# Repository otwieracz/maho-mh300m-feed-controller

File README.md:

# MAHO MH300M Feedrate Controller

## 1. Introduction

### 1.1 Purpose

The MH300M Feedrate Controller is designed to precisely align the panel readings for feed control on the MAHO MH300M milling machine with the voltage output for the tachogenerator. This ensures that the machine operates with accurate and reliable feed rates after the original BBbC LE 10 b-E driver was replaced with a Parker 512C driver.

### 1.2 Overview

This device is retrofitted into the control box of the MAHO MH300M, requiring no changes to the existing wiring. It connects to the Parker 512C driver, the machine's potentiometer, and the control panel's RAPID and CREEP (1/100) buttons. The device converts arbitrary potentiometer values into a calibrated voltage output, ensuring that the machine's feed rates are consistent and accurate.

### 1.3 MAHO MH300M Control Panel

10. Creep feed rate switch (1/1 - 1/100). *Note: MAHO MH300M Feedrate Controller reduces the feed rate by a factor of 10 instead of 100 when in Creep Mode.*
11. Rapid feed rate switch.
12. Feedrate potentiometer.

## 2. Device Components and Connections

### 2.1 Connectors

The device has the following connectors:

- **512C Connector**: 
  - +10V Reference (maximum 5mA)
  - Analog Setpoint (output from the device)
  - Ground (GND)
- **Potentiometer Connector**: Connects to the machine's potentiometer.
- **RAPID and CREEP Button Connectors**: Connects to the control panel's RAPID and CREEP (1/100) buttons.
- **Clear EEPROM Button**: Used to reset the device's configuration stored in EEPROM.

### 2.2 LED Indicator

The device includes an LED indicator used to convey various status messages during setup and operation. The LED blinks in specific patterns to communicate different messages.

## 3. Configuration and Calibration

### 3.1 Initial Setup

Upon installation, the device requires calibration to match the feed rates of the milling machine with the appropriate voltage output. This calibration process is stored in the device's EEPROM, ensuring that the settings persist even after power cycles.

### 3.2 Clearing EEPROM

If you need to reset the device to its default configuration, press and hold the **Clear EEPROM** button while powering on the device. This will erase all stored settings and reset the device to its factory state.

**Note:** Clearing the EEPROM will require recalibration.

### 3.3 Calibration Procedures

Calibration is done in two main steps: configuring the digital potentiometer and setting the ADC steps.

#### 3.3.1 Digital Potentiometer Calibration

1. **Minimum Feed Rate Calibration**: 
   - The **Minimum Feed Rate** is the lowest feed rate at which the milling machine can operate stably. This feed rate is crucial as it ensures that the machine can perform slow movements without stalling, particularly under heavy loads.
   - To accurately determine the minimum feed rate, it's recommended to run all axes simultaneously, especially the Z-axis moving upward, as this simulates the heaviest load.
   - The device will enter the calibration mode for the minimum feed rate (in mm/min).
   - The LED will blink a long-short pattern (`-.`).
   - The device reads the analog input for 30 seconds to determine the minimum digital potentiometer value necessary to maintain stable operation.

2. **500 mm/min Feed Rate Calibration**:
   - The 500 mm/min feed rate serves as a key reference point. This feed rate corresponds to a voltage output of **4.16V** at the terminals of the Parker 512C.
   - The LED will blink a short-long pattern (`.-`).
   - To accurately measure this, connect a voltmeter to the 512C terminals to account for any voltage drop between the control box and the driver.
   - The device adjusts the potentiometer until the voltmeter reads exactly 4.16V, ensuring that the machine's feed rate is precisely 500 mm/min.

#### 3.3.2 ADC Steps Calibration

The device divides the feed rate range into 16 steps, each representing a specific feed rate.

1. **Step Calibration**:
   - For each step, the device reads the analog input for 5.5 seconds.
   - The LED will blink a long-long pattern (`--`) during each step.
   - For each step, set the potentiometer `10` on control panel to the corresponding feed rate (0, 12.5, 20, 31, 40, 50, 63, 80, 100, 125, 160, 200, 250, 315, 400, 500 mm/min).
   - The device will automatically store the ADC value corresponding to each feed rate in the EEPROM.

#### 3.3.3 EEPROM Storage

Once calibration is complete, the device will store the configuration in EEPROM, indicated by two short blinks (`..`). The device will then use this configuration to convert potentiometer values into the appropriate voltage output.

### 3.4 Manual Calibration and Monitoring via UART

#### 3.4.1 Overview

The UART interface is the primary method for monitoring and configuring the MH300M Feedrate Controller. This interface allows you to observe real-time status messages during the calibration process and verify the configuration settings. You can use any UART-capable device, such as a USB-to-UART adapter or a device like the Flipper Zero, to connect to the controller and monitor the serial output.

#### 3.4.2 Setting Up UART Communication

To begin using UART communication:

1. **Connect the Device**:
   - Connect the device's UART pins to your computer using a USB-to-UART adapter or to a handheld UART interface like the Flipper Zero.
   - Ensure the connection uses the correct UART pins (TX, RX, GND).

2. **Open a Serial Terminal**:
   - Open a serial terminal program on your computer (such as PuTTY, Tera Term, or the Arduino IDE's Serial Monitor).
   - Set the baud rate to **9600**.
   - Configure the terminal for **8 data bits, no parity, and 1 stop bit** (8N1).

3. **Start the Device**:
   - Power on the device. The serial terminal will begin displaying messages as the device goes through its initialization and calibration process.

#### 3.4.3 Calibration Process and UART Messages

The calibration process involves several steps, each of which is communicated via the UART interface. Below is a detailed breakdown of the calibration process, along with the messages you will see in the UART terminal.

1. **Initialization**:
   - **Starting Message**:
     - **UART Message**: `starting`
     - Description: Indicates that the device has powered on and is beginning the setup process.
   - **Button Setup**:
     - **UART Message**: `setting up buttons`
     - Description: The device configures the input pins for the RAPID, CREEP, and CLEAR EEPROM buttons.

2. **Configuration Reading**:
   - **Valid Configuration**:
     - **UART Message**: `valid config`
     - Description: Indicates that the device successfully read a valid configuration from the EEPROM.
   - **Invalid Configuration**:
     - **UART Message**: `invalid configuration`
     - Description: The configuration in the EEPROM is either missing or corrupt, triggering the initialization of a new calibration process.

3. **Calibration Steps**:
   - **Digital Potentiometer Minimum Calibration**:
     - **UART Message**: `initializing configuration`
     - Description: The device begins the calibration process.
     - **UART Message**: `config.digipot_min: <value>`
     - Description: The device determines and displays the minimum digital potentiometer value required for stable operation.
   - **Digital Potentiometer 500 mm/min Calibration**:
     - **UART Message**: `config.digipot_500: <value>`
     - Description: The device calculates and displays the digital potentiometer value corresponding to a 500 mm/min feed rate.
   - **ADC Setpoint Calibration**:
     - **UART Message**: `config.feed_<feed_rate>: <adc_value>`
     - Description: For each step in the feed rate table, the device reads and displays the corresponding ADC value. This process repeats for each of the 16 predefined steps.
   - **Completion Message**:
     - **UART Message**: `initialization complete`
     - Description: Indicates that the calibration process has finished successfully, and the configuration has been stored in the EEPROM.

#### 3.4.4 Operation Monitoring via UART

During normal operation, the UART interface continues to output real-time status messages, allowing you to monitor the device's performance:

- **Feed Rate and Voltage Output**:
  - **UART Message**: `fr: <feedrate>mm/min / <voltage>V`
  - Description: Displays the current feed rate in mm/min and the corresponding voltage output to the Parker 512C.

#### 3.4.5 Troubleshooting via UART

Use the UART messages to diagnose issues:

- If the device repeatedly outputs `invalid configuration`, ensure that the EEPROM is not corrupted or repeatedly reset.
- Monitor the feed rate and voltage messages to verify that the device operates as expected under different conditions (e.g., with RAPID or CREEP buttons pressed).

### 3.4.6 Flowchart of the Calibration Process with UART Monitoring

```mermaid
graph TD
    A[Power On] --> B{Clear EEPROM Button Pressed?}
    B -- Yes --> C[Clear EEPROM and Reset Configuration]
    B -- No --> D[Read Configuration from EEPROM]
    D -- Invalid --> E[Initialize Calibration]
    E --> F[Calibrate Digipot Min]
    F --> G[Calibrate Digipot 500 mm/min]
    G --> H[Calibrate ADC Setpoints]
    H --> I[Save Configuration to EEPROM]
    D -- Valid --> J[Start Operation]
    I --> J
    J --> K[Monitor Potentiometer Values]
    K --> L[Calculate Feedrate]
    L --> M[Convert Feedrate to Digipot Value]
    M --> N[Output Voltage to 512C]
```

## 4. Operation

### 4.1 Normal Operation

Once configured, the device operates automatically, continuously converting the potentiometer's analog signal into a precise voltage output that drives the tachogenerator. This output is based on the calibrated settings stored in EEPROM.

### 4.2 Button Functions

- **RAPID Button**: When pressed, the feed rate is set to 1200 mm/min, overriding the potentiometer setting.
- **CREEP Button**: When pressed, the feed rate is reduced by a factor of 10.

### 4.3 Power Saving Mode

The device enters a low-power state between readings to conserve energy. This does not affect the device's performance but ensures it operates efficiently.

## 5. Maintenance and Troubleshooting

### 5.1 Regular Maintenance

The device requires minimal maintenance. Periodically check the connectors and wiring to ensure they are secure and free of damage.

### 5.2 Troubleshooting

- **No Output Voltage**: Verify that the device is receiving power and that the potentiometer is functioning correctly.
- **Incorrect Feed Rate**: Re-run the calibration procedure to ensure the settings are accurate.
- **LED Indicator Not Blinking**: Check the LED connections and ensure the device is powered on.

## 6. Technical Specifications

- **Input Voltage**: 10V from the Parker 512C
- **Analog Setpoint Output Range**: 0-10V
- **Maximum Current Draw**: 5mA from the 10V reference
- **EEPROM Storage**: Non-volatile memory storing calibration settings
- **Power Saving Mode**: Automatic, with 250ms sleep cycles

## 7. Safety Information

- Ensure all connections are secure before powering on the device.
- Do not attempt to modify the device's hardware.
- Use the device only for its intended purpose with the MAHO MH300M milling machine.

## Chapter 8: Programming the MH300M Feedrate Controller

### 8.1 Overview

Programming the MH300M Feedrate Controller involves configuring the microcontroller, setting fuse bits, and uploading the firmware. This chapter provides general guidelines on how to perform these tasks using standard AVR/Arduino practices.

### 8.2 Fuse Settings

Fuse settings are crucial for defining how the microcontroller operates at a hardware level. The fuses should be set to ensure the following:

- **Clock Source**: The microcontroller should use the internal oscillator with a specific clock divider to achieve the desired operating frequency (e.g., 1 MHz).
- **Bootloader Settings**: The fuses should be configured to allow the microcontroller to use a bootloader, if applicable.
- **EEPROM Retention**: Ensure that the EEPROM data is preserved during a chip erase.
- **Brown-Out Detection**: Configure the Brown-Out Detection (BOD) settings according to the requirements, or disable it if not needed.

These settings are typically configured using low, high, and extended fuse bits. Proper fuse settings ensure that the device runs at the correct speed, retains necessary data, and operates reliably under different power conditions.

### 8.3 Build Configuration

When building the firmware for the MH300M Feedrate Controller, the following flags and settings should be considered:

- **Microcontroller Type**: Ensure that the target microcontroller (e.g., ATmega328P) is correctly specified in the build configuration.
- **CPU Frequency**: Set the CPU frequency to match the hardware configuration (e.g., 1 MHz).
- **Build Flags**: Include any necessary build flags to define specific operational parameters or to include/exclude certain features.
  - For example, you might use a flag to specify that the firmware is built for a specific Arduino variant or to control how certain libraries behave.
- **Libraries**: Ensure all required libraries are included, such as those for low-power management or for controlling peripheral devices like digital potentiometers.

### 8.4 Firmware Upload

The firmware can be uploaded to the microcontroller using either an ISP programmer or via a bootloader using a USB-to-UART converter.

- **ISP Upload**: Use an In-System Programmer (ISP) to directly flash the firmware onto the microcontroller. This method allows for full control, including setting fuse bits.
- **UART Upload**: If using a bootloader, upload the firmware via a USB-to-UART converter. Ensure that the correct upload protocol (e.g., stk500v1) and baud rate (e.g., 9600) are set.

During the upload process, you may need to specify additional flags for the upload tool to correctly communicate with the microcontroller and write the firmware.

### 8.5 Final Steps

After programming:

1. **Verify Fuse Settings**: Ensure that the fuse settings are correctly applied.
2. **Test the Device**: Power on the device and verify basic functionality, such as LED indicators and response to input signals.
3. **Monitor Output**: If applicable, use a UART interface to monitor the device’s startup messages and operational status.

By following these general guidelines, you can ensure that the MH300M Feedrate Controller is programmed correctly and operates as intended.

# Appendix A: Schematics

The following schematics detail the connections and components used in the MH300M Feedrate Controller:

# Appendinx B: Bill of Materials

|Id |Designator|Footprint                                       |Quantity|Designation      |
|---|----------|------------------------------------------------|--------|-----------------|
|1  |C1        |CP_Radial_D4.0mm_P2.00mm                        |1       |10uF 16V         |                |      |      |
|2  |J4        |JST_XH_B3B-XH-A_1x03_P2.50mm_Vertical           |1       |UART             |                |      |      |
|3  |R1        |R_Axial_DIN0207_L6.3mm_D2.5mm_P7.62mm_Horizontal|1       |R8K3             |                |      |      |
|4  |U1        |TSSOP14_MC_MCH                                  |1       |MCP41HV51-103E/ST|                |      |      |
|5  |J1        |TerminalBlock_bornier-4_P5.08mm                 |1       |CREEP/RAPID      |                |      |      |
|6  |J3        |TerminalBlock_bornier-3_P5.08mm                 |1       |POT              |                |      |      |
|7  |PRO_MINI1 |Arduino_Pro_Mini (3V3, 8MHz)                    |1       |~                |                |      |      |
|8  |C3        |C_Disc_D5.0mm_W2.5mm_P2.50mm                    |1       |100nF            |                |      |      |
|9  |SW1       |SW_PUSH_6mm                                     |1       |CLEAR_EEPROM     |                |      |      |
|10 |J2        |TerminalBlock_bornier-3_P5.08mm                 |1       |512C             |                |      |      |
|11 |D1        |LED_D5.0mm                                      |1       |LED              |                |      |      |

# Appendix C: PCB Layout

## Top Layer

## Bottom Layer

# Appendix D: Case sticker

# Appendix E: Firmware Source Code

## `include/blinkmsg.h`
```cpp
#ifndef BLINKMSG_H
#define BLINKMSG_H

enum BLINKMSG {
  BLINKMSG_CONFIG_OK,
  BLINKMSG_SETUP_DIGIPOT_MIN,
  BLINKMSG_SETUP_DIGIPOT_500,
  BLINKMSG_SETUP_ADC_SETPOINT,
};

void blinkmsg(int blinkmsg);
#endif
```

## `include/config.h`
```cpp
// Arduino Mega 2560
#ifdef ARDUINO_AVR_MEGA2560
#define ANALOG_PIN A0
#define RAPID_BTN_PIN 52
#define CREEP_BTN_PIN 53
#define CLEAR_EEPROM_BTN_PIN 51
#define CS_PIN 10
#define SHDN_PIN 54
#define LED_PIN 55
#endif

// Arduino Pro Mini 3.3V 8MHz
#ifdef ARDUINO_AVR_PRO
#define ANALOG_PIN A0
#define RAPID_BTN_PIN 5
#define CREEP_BTN_PIN 4
#define CLEAR_EEPROM_BTN_PIN 9
#define CS_PIN 10
// #define SHDN_PIN 6
// #define LED_PIN 5
#define SHDN_PIN 3
#define LED_PIN 2
#endif
```

## `src/main.cpp`
```cpp
#include <Arduino.h>
#include <EEPROM.h>
#include <LowPower.h>
#include <MCP41HVX1.h>
#include <SPI.h>
#include <blinkmsg.h>
#include <config.h>

MCP41HVX1 digipot(CS_PIN, SHDN_PIN, MCP41HVX1_PIN_NOT_CONFIGURED);

#define ADC_MAX 1023
#define DIGIPOT_MAX 255

#define N_STEPS 16    // Number of steps in the conversion table
#define RAPID 1200    // Rapid feed rate in mm/min
#define CREEP_DIV 10  // Creep feed rate divisor

#define CONFIG_VERSION 2
struct EepromConfig {
  int version;
  int digipot_min;  // Minimum digipot value for stable feed rate (15bit)
  int digipot_500;  // digipot value for 500mm/min feed rate - 4.16V measured at
                    // controller (15bit)
  int adc_setpoint[N_STEPS];  // ADC setpoint for each step in the conversion
                              // table
};

// ADC setpoints (feed rate) for each step in the conversion table
// note: 12mm/min is used instead of 12.5mm/min to avoid floating point
// arithmetic
int feed_table[N_STEPS] = {0,   12,  20,  31,  40,  50,  63,  80,
                           100, 125, 160, 200, 250, 315, 400, 500};

// Config - unititialized, to be read from EEPROM
EepromConfig config;

//
// Setup functions
//

// Reset configuration
void reset_eeprom_config(int addr) {
  EepromConfig default_config = {
      .version = 0, .digipot_min = 0, .digipot_500 = 0, .adc_setpoint = {0}};
  EEPROM.put(addr, default_config);
}

// Read config from EEPROM
bool read_config(EepromConfig *config) {
  int addr = 0;

  // Reset configuration if CLEAR_EEPROM button is pressed
  if (digitalRead(CLEAR_EEPROM_BTN_PIN) == LOW) {
    Serial.println("resetting configuration");
    reset_eeprom_config(addr);
    return false;
  }

  EepromConfig eeprom_config;
  EEPROM.get(addr, eeprom_config);
  if (eeprom_config.version == CONFIG_VERSION) {
    Serial.println("valid config");
    blinkmsg(BLINKMSG_CONFIG_OK);
    *config = eeprom_config;
    return true;
  } else {
    Serial.println("invalid configuration");
    return false;
  }
}

// Write empty config to EEPROM with version 0, enforcing reinitialization
void reset_eeprom_config() {
  EepromConfig default_config = {
      .version = 0, .digipot_min = 0, .digipot_500 = 0, .adc_setpoint = {0}};
  EEPROM.put(0, default_config);
}

// Setup buttons
void setup_buttons() {
  Serial.println("setting up buttons");
  pinMode(RAPID_BTN_PIN, INPUT_PULLUP);
  pinMode(CREEP_BTN_PIN, INPUT_PULLUP);
  pinMode(CLEAR_EEPROM_BTN_PIN, INPUT_PULLUP);
  pinMode(LED_PIN, OUTPUT);
  digitalWrite(LED_PIN, HIGH);
}

//
// Calibration procedures
//

// Calibrate digital potentionmeter
int calibrate_digipot(const char *name, unsigned int wait_time) {
  Serial.print("config.");
  Serial.print(name);
  Serial.print(": ");
  Serial.flush();

  // Keep reading the analog input for wait_time ms
  unsigned long start = millis();
  int digipot_out = 0;
  while (millis() - start < wait_time) {
    int adc_in = analogRead(ANALOG_PIN);
    digipot_out = map(adc_in, 0, ADC_MAX, 0, DIGIPOT_MAX);
    digipot.WiperSetPosition(digipot_out);
    delay(100);
  }

  Serial.println(digipot_out);

  return digipot_out;
}

// Calibrate ADC steps
//
void calibrate_adc_step(unsigned int step, int *buf, unsigned int wait_time) {
  int feed = feed_table[step];

  Serial.print("config.feed_");
  Serial.print(feed);
  Serial.print(": ");

  // Keep reading the analog input for wait_time ms
  unsigned long start = millis();
  int adc_in = 0;
  while (millis() - start < wait_time) {
    adc_in = analogRead(ANALOG_PIN);
    delay(100);
  }

  buf[step] = adc_in;

  Serial.println(adc_in);
}

void initialize_config() {
  Serial.println("initializing configuration");
  blinkmsg(BLINKMSG_SETUP_DIGIPOT_MIN);
  int digipot_min = calibrate_digipot("digipot_min", 30000);
  blinkmsg(BLINKMSG_SETUP_DIGIPOT_500);
  int digipot_500 = calibrate_digipot("digipot_500", 30000);

  EepromConfig new_config = {.version = CONFIG_VERSION,
                             .digipot_min = digipot_min,
                             .digipot_500 = digipot_500,
                             .adc_setpoint = {0}};

  for (int i = 0; i < N_STEPS; i++) {
    blinkmsg(BLINKMSG_SETUP_ADC_SETPOINT);
    calibrate_adc_step(i, new_config.adc_setpoint, 5500);
  }

  blinkmsg(BLINKMSG_CONFIG_OK);
  EEPROM.put(0, new_config);
}

// Value mapping
//

// For given ADC input range, return the id of the lower bound
// of the range that contains the value
int find_range(int adc_value) {
  // Example:
  // adc_setpoint = {0, 100, 200, 300}
  // adc_value = 150
  // [1]:100 < adc_value:150 <= [2]:200
  // return 1

  for (int i = 0; i < N_STEPS - 1; i++) {
    if (config.adc_setpoint[i] < adc_value &&
        adc_value <= config.adc_setpoint[i + 1]) {
      return i;
    }
  }
  return 0;
}

// For given ADC value, return the feedrate in mm/min
// based on the conversion table and the current setpoint
// and the state of the rapid and creep buttons
int feedrate() {
  int adc_value = analogRead(ANALOG_PIN);
  int range_id = find_range(adc_value);

  bool rapid = digitalRead(RAPID_BTN_PIN) == LOW;
  bool creep = digitalRead(CREEP_BTN_PIN) == LOW;

  int feedrate = 0;

  if (rapid) {
    feedrate = RAPID;
  } else if (adc_value < config.adc_setpoint[1]) {
    /* Round adc values for feeds lower than 12mm/min (between 0 and first step)
     * to 0 to avoid feedrate oscillation */
    feedrate = 0;
  } else if (adc_value == 0) {
    feedrate = 0;
  } else {
    feedrate = map(adc_value, config.adc_setpoint[range_id],
                   config.adc_setpoint[range_id + 1], feed_table[range_id],
                   feed_table[range_id + 1]);
  }

  if (creep && !rapid) {
    feedrate = feedrate / CREEP_DIV;
  }
  return feedrate;
}

// Convert feedrate in mm/min to digipot value
// based on the current configuration
// If reported feedrate is non-zero, but the calculated digipot value is below
// the minimum, return the minimum digipot value to ensure stable operation
long int feedrate_to_digipot(int feedrate) {
  long feed_digipot = (long)feedrate * (long)config.digipot_500 / 500;

  if (feedrate == 0) {
    return 0;
  } else if (feed_digipot > DIGIPOT_MAX) {
    return DIGIPOT_MAX;
  } else if (feed_digipot > 0 && feed_digipot < config.digipot_min) {
    return config.digipot_min;
  } else {
    return feed_digipot;
  }
}

bool setup_complete = false;

void setup() {
  Serial.begin(9600);
  Serial.println("starting");
  Serial.flush();
  setup_buttons();

  if (!read_config(&config)) {
    initialize_config();
    read_config(&config);
  }

  Serial.flush();
}

void loop() {
  int feedrate_val = feedrate();
  long int digipot_value = feedrate_to_digipot(feedrate_val);
  long int mv = map(digipot_value, 0, DIGIPOT_MAX, 0, 10000);

  if (digipot_value > 0) {
    digipot.ResistorNetworkEnable();
    digipot.WiperSetPosition(digipot_value);
  } else {
    digipot.ResistorNetworkDisable();
  }

  int v = mv / 1000;
  int v_mod = mv % 1000;
  char buf[64];
  sprintf(buf, "fr: %4dmm/min / %1d.%02dV", feedrate_val, v, v_mod / 10);
  Serial.println(buf);
  Serial.flush();

  LowPower.powerDown(SLEEP_250MS, ADC_OFF, BOD_OFF);
}
```

## `src/blinkmsg.cpp`
```cpp
#include <Arduino.h>
#include <blinkmsg.h>
#include <config.h>

#define MESSAGE_LENGTH 1000
#define MESSAGE_SHORT 100
#define MESSAGE_LONG 700

//
// LED messages
//

void blink_led(const char *msg) {
  for (int i = 0; i < 2; i++) {
    if (msg[i] == '.') {
      digitalWrite(LED_PIN, LOW);
      delay(MESSAGE_SHORT);
      digitalWrite(LED_PIN, HIGH);
      delay(MESSAGE_LENGTH - MESSAGE_SHORT);
    } else if (msg[i] == '-') {
      digitalWrite(LED_PIN, LOW);
      delay(MESSAGE_LONG);
      digitalWrite(LED_PIN, HIGH);
      delay(MESSAGE_LENGTH - MESSAGE_LONG);
    }
  }
}

void blinkmsg(int blinkmsg) {
  switch (blinkmsg) {
    case BLINKMSG_CONFIG_OK:
      blink_led("..");
      break;
    case BLINKMSG_SETUP_DIGIPOT_MIN:
      blink_led("-.");
      break;
    case BLINKMSG_SETUP_DIGIPOT_500:
      blink_led(".-");
      break;
    case BLINKMSG_SETUP_ADC_SETPOINT:
      blink_led("--");
      break;
  }
}
```

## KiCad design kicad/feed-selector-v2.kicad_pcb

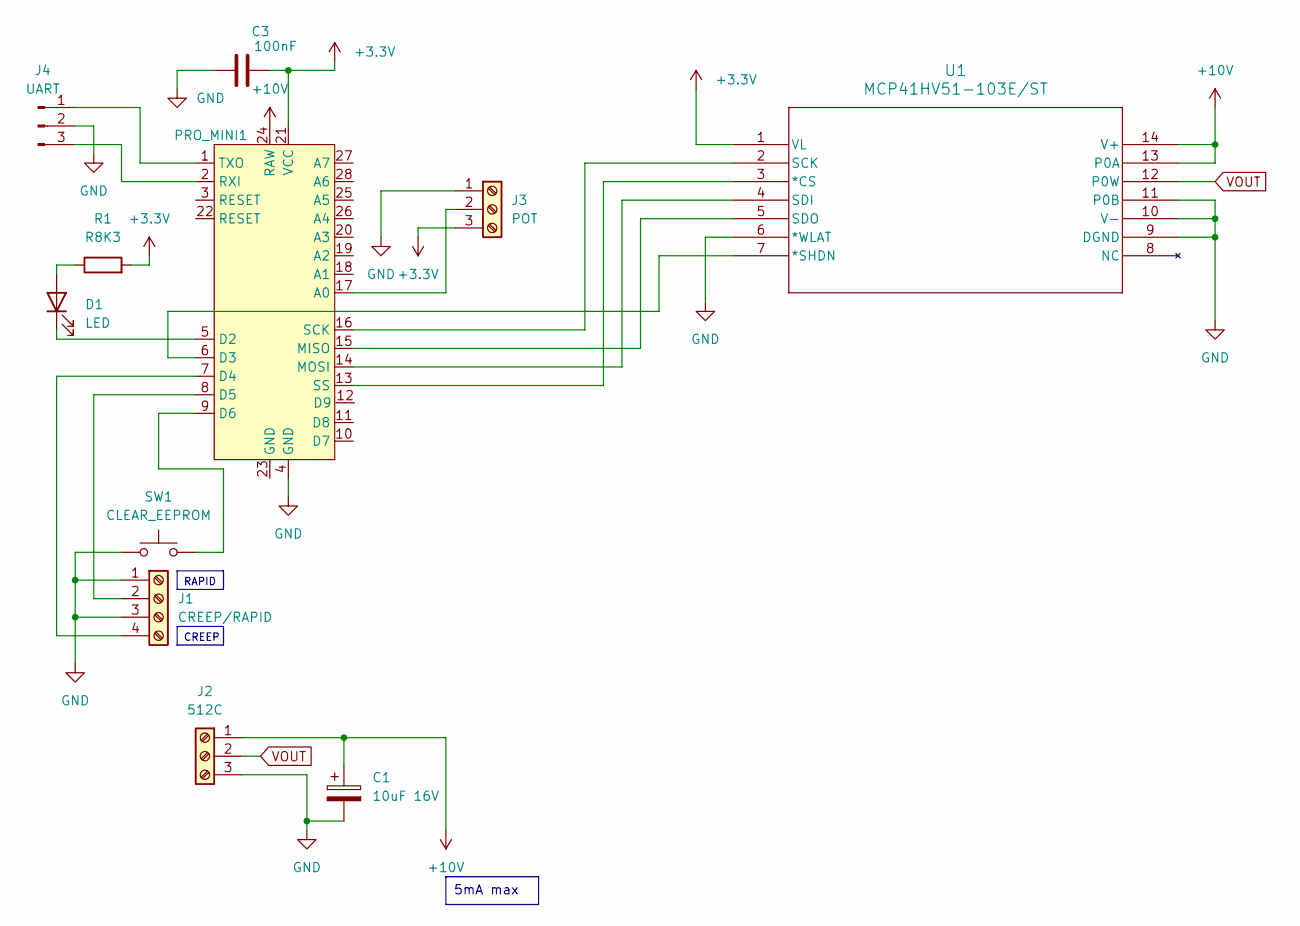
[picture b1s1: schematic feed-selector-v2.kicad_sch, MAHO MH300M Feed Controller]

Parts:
C1: 10uF 16V; CP_Radial_D4.0mm_P2.00mm
C3: 100nF; C_Disc_D5.0mm_W2.5mm_P2.50mm
D1: LED; LED_D5.0mm
J1: CREEP/RAPID; TerminalBlock_bornier-4_P5.08mm
J2: 512C; TerminalBlock_bornier-3_P5.08mm
J3: POT; TerminalBlock_bornier-3_P5.08mm
J4: UART; JST_XH_B3B-XH-A_1x03_P2.50mm_Vertical
PRO_MINI1: Arduino_Pro_Mini
R1: R8K3; R_Axial_DIN0207_L6.3mm_D2.5mm_P7.62mm_Horizontal
SW1: CLEAR_EEPROM; SW_PUSH_6mm
U1: MCP41HV51-103E/ST; TSSOP14_MC_MCH

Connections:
+3.3V: C3.2, J3.3, PRO_MINI1.21 (VCC), R1.2, U1.1 (VL)
+10V: C1.1, J2.1, PRO_MINI1.24 (RAW), U1.13 (P0A), U1.14 (V+)
GND: C1.2, C3.1, J1.1, J1.3, J2.3, J3.1, J4.2, PRO_MINI1.4 (GND), SW1.1, U1.6 (*WLAT), U1.9 (DGND), U1.10 (V-), U1.11 (P0B)
unnamed: D1.2 (A), R1.1
unnamed: D1.1 (K), PRO_MINI1.5 (D2)
unnamed: J1.2, PRO_MINI1.8 (D5)
unnamed: J1.4, PRO_MINI1.7 (D4)
unnamed: J3.2, PRO_MINI1.17 (A0)
unnamed: J4.1, PRO_MINI1.1 (TXO)
unnamed: J4.3, PRO_MINI1.2 (RXI)
unnamed: PRO_MINI1.6 (D3), U1.7 (*SHDN)
unnamed: PRO_MINI1.9 (D6), SW1.2
unnamed: PRO_MINI1.13 (SS), U1.3 (*CS)
unnamed: PRO_MINI1.14 (MOSI), U1.4 (SDI)
unnamed: PRO_MINI1.15 (MISO), U1.5 (SDO)
unnamed: PRO_MINI1.16 (SCK), U1.2 (SCK)
VOUT: J2.2, U1.12 (P0W)

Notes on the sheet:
RAPID
CREEP
5mA max

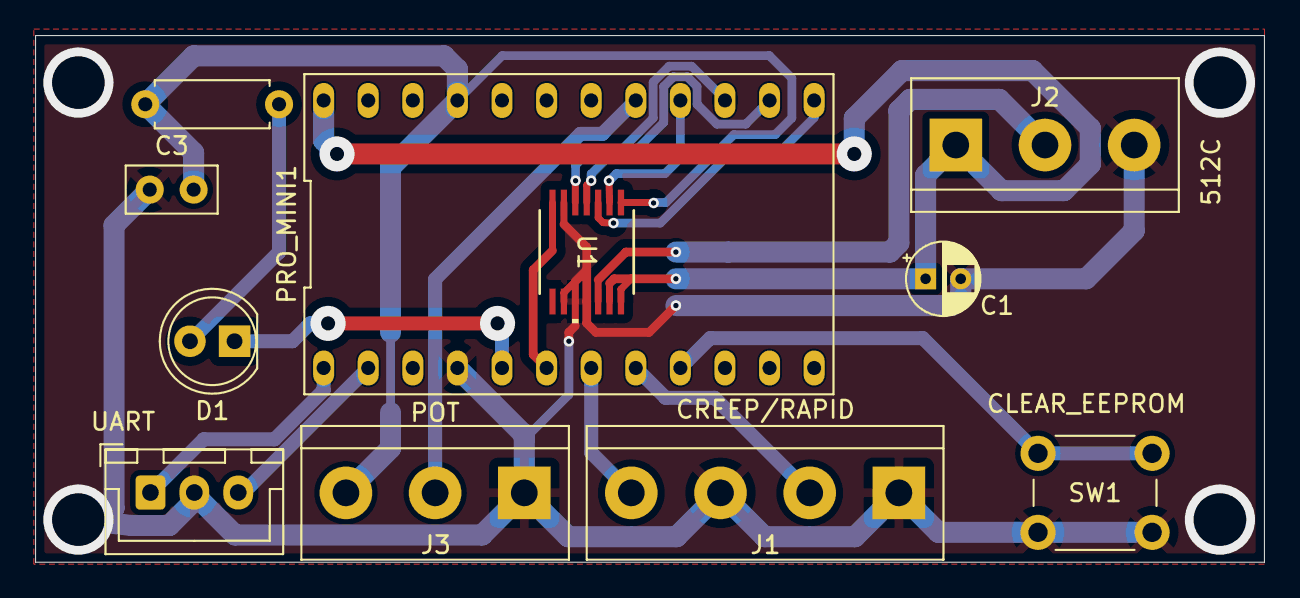
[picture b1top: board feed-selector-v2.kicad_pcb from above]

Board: 2 copper layers, 70.0 x 30.0 mm, 11 parts (0 on the bottom side), 17 nets.

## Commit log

2024-06-24 complete calibration
2024-06-25 adc -> feerate conversion
2024-06-25 rapid and creep feed
2024-06-29 proof of concept operational
2024-07-13 digipot with blinkmsg
2024-07-14 Switch to 1MHz, internal oscillator
2024-09-03 all issues fixed
2024-09-05 documentation
